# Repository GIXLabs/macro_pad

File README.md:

# A place for the GIX Pico Pad Workshop content
In this workshop, we will be making a 4-button macro keypad that you can program yourself.

## Bill of Materials (BOM)
- Raspberry Pi Pico
- 4x surface mount tactile switch
- GIX PicoPad PCB
- Solder paste stencil
- Credit card (or other plastic straight edge)
- Lead-free solder paste

## Libraries needed

Download bundle library [here](https://circuitpython.org/libraries)

Before continuing make sure your board's lib folder has the following libraries:

- adafruit_hid
- adafruit_debouncer
- adafruit_ticks

## Setup
1. 3D print a stencil holder (in the cad folder) for each stencil.
1. Many stencils come as one large sheet. We recommend carefully cutting the stencil down to a more manageable size using a pair of sheet metal shears.
1. Since the cut edges can be quite sharp, wrap the sharp edges in tape.
1. We recommend baking many of the Raspberry Pi Picos to the main board ahead of the event as this adds a particularly long step.
    1. Either hot plate or reflow oven will work. 

## Steps
1. Place the board in the stencil holder and lower the stencil over it. The pads on the board should match the holes in the stencil.
1. Squeeze a thick line of solder paste across one side of the stencil.
1. Using a credit card or similar piece of plastic, swipe the solder paste across the stencil.
1. Lift the stencil to reveal a board with solder paste on its pads.
1. Using tweezers, drop the tactile switch on the solder paste. Positioning does not have to be perfect as surface tension will pull the part into place.
1. Using a hot air gun set to 450 F, heat the solder paste at each switch until it shimmers and turns silver. Don't worry about the solder paste spreading out as it gets hot.
1. If the keypad does not call itself CIRCUITPY when you plug it in, you will need to copy and paste the UF2 file found [here](https://learn.adafruit.com/pico-four-key-macropad/circuitpython) to the drive.
1. Install the libraries by dragging them into the `lib` folder on the CIRCUITPY drive.
1. Download the code from [here](https://learn.adafruit.com/pico-four-key-macropad/code-the-four-keypad) and put it in the CIRCUITPY drive. Make sure to name it `code.py`.

## References

[Pico Four Keypad](https://learn.adafruit.com/pico-four-key-macropad/overview)

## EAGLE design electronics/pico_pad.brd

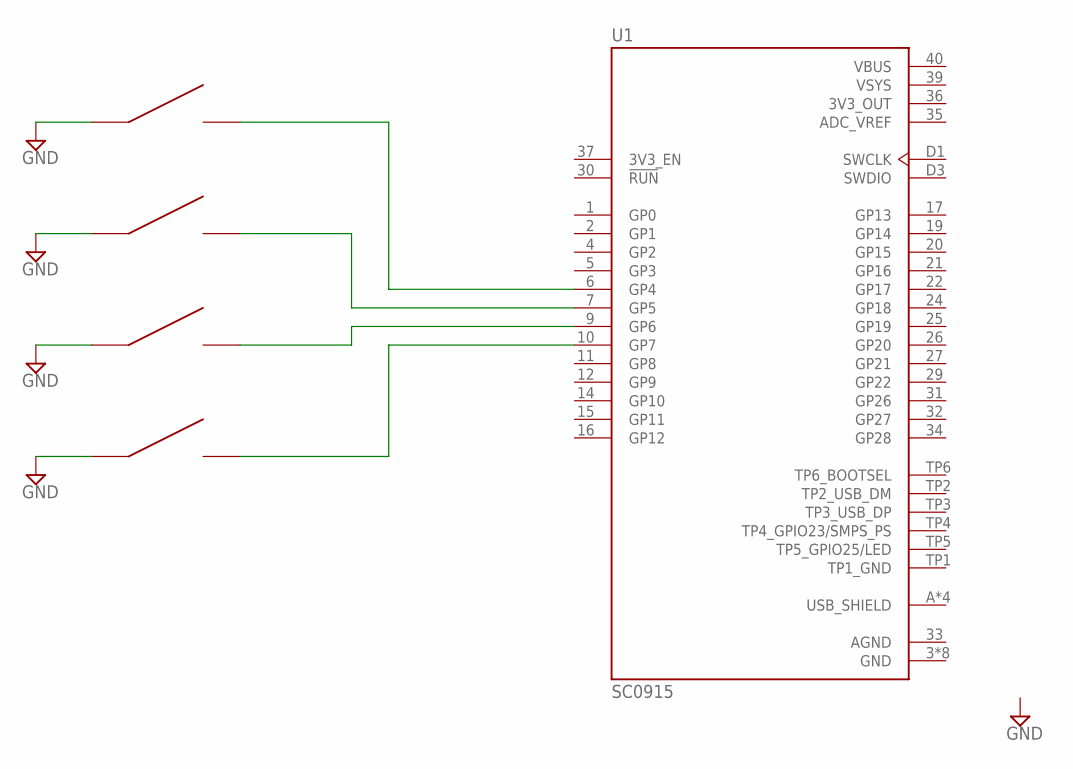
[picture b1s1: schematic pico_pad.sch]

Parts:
U1: SC0915; MODULE_SC0915
U$1, U$2, U$3, U$4: PTS526_TACT

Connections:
3V3_OUT: U1.36 (3V3_OUT)
ADC_VREF: U1.35 (ADC_VREF)
AGND: U1.33 (AGND)
GND: U1.3 (GND), U1.8 (GND), U1.13 (GND), U1.18 (GND), U1.23 (GND), U1.28 (GND), U1.38 (GND), U1.D2 (GND), U$1.A1 (A), U$1.A2 (A), U$2.A1 (A), U$2.A2 (A), U$3.A1 (A), U$3.A2 (A), U$4.A1 (A), U$4.A2 (A)
unnamed: U1.6 (GP4), U$2.B1 (B), U$2.B2 (B)
unnamed: U1.7 (GP5), U$3.B1 (B), U$3.B2 (B)
unnamed: U1.9 (GP6), U$1.B1 (B), U$1.B2 (B)
unnamed: U1.10 (GP7), U$4.B1 (B), U$4.B2 (B)
TP1_GND: U1.TP1 (TP1_GND)
USB_SHIELD: U1.A (USB_SHIELD), U1.B (USB_SHIELD), U1.C (USB_SHIELD), U1.D (USB_SHIELD)
VBUS: U1.40 (VBUS)
VSYS: U1.39 (VSYS)

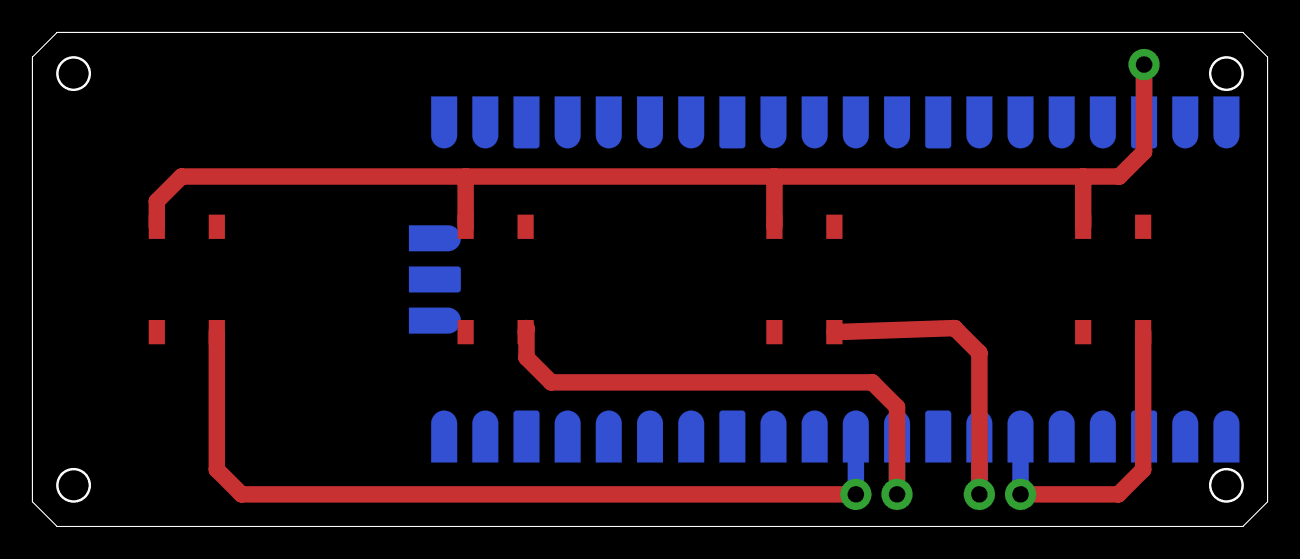
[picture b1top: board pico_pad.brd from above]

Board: 2 copper layers, 76.0 x 30.3 mm, 5 parts (1 on the bottom side), 6 nets.

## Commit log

2022-10-25 Initial commit.
2022-10-25 Added more steps to README.md
